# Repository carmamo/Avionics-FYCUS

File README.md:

<!-- Improved compatibility of back to top link: See: https://github.com/othneildrew/Best-README-Template/pull/73 -->

<!--
*** Thanks for checking out the Best-README-Template. If you have a suggestion
*** that would make this better, please fork the repo and create a pull request
*** or simply open an issue with the tag "enhancement".
*** Don't forget to give the project a star!
*** Thanks again! Now go create something AMAZING! :D
-->

<!-- PROJECT SHIELDS -->
<!--
*** I'm using markdown "reference style" links for readability.
*** Reference links are enclosed in brackets [ ] instead of parentheses ( ).
*** See the bottom of this document for the declaration of the reference variables
*** for contributors-url, forks-url, etc. This is an optional, concise syntax you may use.
*** https://www.markdownguide.org/basic-syntax/#reference-style-links
-->
[![Contributors][contributors-shield]][contributors-url]
[![Forks][forks-shield]][forks-url]
[![Stargazers][stars-shield]][stars-url]
[![Issues][issues-shield]][issues-url]
[![MIT License][license-shield]][license-url]
[![LinkedIn][linkedin-shield]][linkedin-url]

<!-- PROJECT LOGO -->
<br />
<div align="center">

<h3 align="center">Avionics FYCUS</h3>

  <p align="center">
    Hardware and Firmware for a 3U Cubesat
    <br />
    <a href="https://github.com/carmamo/Avionics-FYCUS"><strong>Explore the docs »</strong></a>
    <br />
    <br />
    <a href="https://github.com/carmamo/Avionics-FYCUS">View Demo</a>
    ·
    <a href="https://github.com/carmamo/Avionics-FYCUS/issues">Report Bug</a>
    ·
    <a href="https://github.com/carmamo/Avionics-FYCUS/issues">Request Feature</a>
  </p>
</div>

<!-- TABLE OF CONTENTS -->
<details>
  <summary>Table of Contents</summary>
  <ol>
    <li>
      <a href="#about-the-project">About The Project</a>
      <ul>
        <li><a href="#built-with">Built With</a></li>
      </ul>
    </li>
    <li>
      <a href="#getting-started">Getting Started</a>
      <ul>
        <li><a href="#prerequisites">Prerequisites</a></li>
        <li><a href="#installation">Installation</a></li>
      </ul>
    </li>
    <li><a href="#usage">Usage</a></li>
    <li><a href="#roadmap">Roadmap</a></li>
    <li><a href="#contributing">Contributing</a></li>
    <li><a href="#license">License</a></li>
    <li><a href="#contact">Contact</a></li>
    <li><a href="#acknowledgments">Acknowledgments</a></li>
  </ol>
</details>

<!-- ABOUT THE PROJECT -->
## About The Project
![Product front Screen Shot][product-screenshot-front]
![Product back Screen Shot][product-screenshot-back]
[![Product gui Screen Shot][gui-screenshot]][gui-screenshot]

This project involves the creation of the PCB and firmware for a 3U CubeSat, in collaboration with FYCUS, a team of passionate students at the University of Seville. Our mission is to design, manufacture and operate small satellites, and this project is a critical step in achieving that goal.

Our team will be responsible for the design and implementation of the PCB and firmware, which are essential components of the CubeSat's operation.

<p align="right">(<a href="#readme-top">back to top</a>)</p>

### Built With

<p align="right">(<a href="#readme-top">back to top</a>)</p>

<!-- GETTING STARTED -->
## Getting Started

This is an example of how you may give instructions on setting up your project locally.
To get a local copy up and running follow these simple example steps.

### Prerequisites

This is an example of how to list things you need to use the software and how to install them.
* npm
  ```sh
  npm install npm@latest -g
  ```

### Installation

1. Get a free API Key at [https://example.com](https://example.com)
2. Clone the repo
   ```sh
   git clone https://github.com/carmamo/Avionics-FYCUS.git
   ```
3. Install NPM packages
   ```sh
   npm install
   ```
4. Enter your API in `config.js`
   ```js
   const API_KEY = 'ENER YOUR API';
   ```

<p align="right">(<a href="#readme-top">back to top</a>)</p>

<!-- USAGE EXAMPLES -->
## Usage

Use this space to show useful examples of how a project can be used. Additional screenshots, code examples and demos work well in this space. You may also link to more resources.

_For more examples, please refer to the [Documentation](https://example.com)_

<p align="right">(<a href="#readme-top">back to top</a>)</p>

<!-- ROADMAP -->
## Roadmap

- [ ] Feature 1
- [ ] Feature 2
- [ ] Feature 3
    - [ ] Nested Feature

See the [open issues](https://github.com/carmamo/Avionics-FYCUS/issues) for a full list of proposed features (and known issues).

<p align="right">(<a href="#readme-top">back to top</a>)</p>

<!-- CONTRIBUTING -->
## Contributing

Contributions are what make the open source community such an amazing place to learn, inspire, and create. Any contributions you make are **greatly appreciated**.

If you have a suggestion that would make this better, please fork the repo and create a pull request. You can also simply open an issue with the tag "enhancement".
Don't forget to give the project a star! Thanks again!

1. Fork the Project
2. Create your Feature Branch (`git checkout -b feature/AmazingFeature`)
3. Commit your Changes (`git commit -m 'Add some AmazingFeature'`)
4. Push to the Branch (`git push origin feature/AmazingFeature`)
5. Open a Pull Request

<p align="right">(<a href="#readme-top">back to top</a>)</p>

<!-- LICENSE -->
## License

Distributed under the MIT License. See `LICENSE.txt` for more information.

<p align="right">(<a href="#readme-top">back to top</a>)</p>

<!-- CONTACT -->
## Contact

Your Name - [@twitter_handle](https://twitter.com/twitter_handle) - email@email_client.com

Project Link: [https://github.com/carmamo/Avionics-FYCUS](https://github.com/carmamo/Avionics-FYCUS)

<p align="right">(<a href="#readme-top">back to top</a>)</p>

<!-- ACKNOWLEDGMENTS -->
## Acknowledgments

* 
* 
* 

<p align="right">(<a href="#readme-top">back to top</a>)</p>

<!-- MARKDOWN LINKS & IMAGES -->
<!-- https://www.markdownguide.org/basic-syntax/#reference-style-links -->
[contributors-shield]: https://img.shields.io/github/contributors/carmamo/Avionics-FYCUS.svg?style=for-the-badge
[contributors-url]: https://github.com/carmamo/Avionics-FYCUS/graphs/contributors
[forks-shield]: https://img.shields.io/github/forks/carmamo/Avionics-FYCUS.svg?style=for-the-badge
[forks-url]: https://github.com/carmamo/Avionics-FYCUS/network/members
[stars-shield]: https://img.shields.io/github/stars/carmamo/Avionics-FYCUS.svg?style=for-the-badge
[stars-url]: https://github.com/carmamo/Avionics-FYCUS/stargazers
[issues-shield]: https://img.shields.io/github/issues/carmamo/Avionics-FYCUS.svg?style=for-the-badge
[issues-url]: https://github.com/carmamo/Avionics-FYCUS/issues
[license-shield]: https://img.shields.io/github/license/carmamo/Avionics-FYCUS.svg?style=for-the-badge
[license-url]: https://github.com/carmamo/Avionics-FYCUS/blob/master/LICENSE.txt
[linkedin-shield]: https://img.shields.io/badge/-LinkedIn-black.svg?style=for-the-badge&logo=linkedin&colorB=555
[linkedin-url]: https://www.linkedin.com/company/fycus/?originalSubdomain=es
[gui-screenshot]: images/screenshot2.png
[product-screenshot-front]: images/EPS_front.png
[product-screenshot-back]: images/EPS_back.png

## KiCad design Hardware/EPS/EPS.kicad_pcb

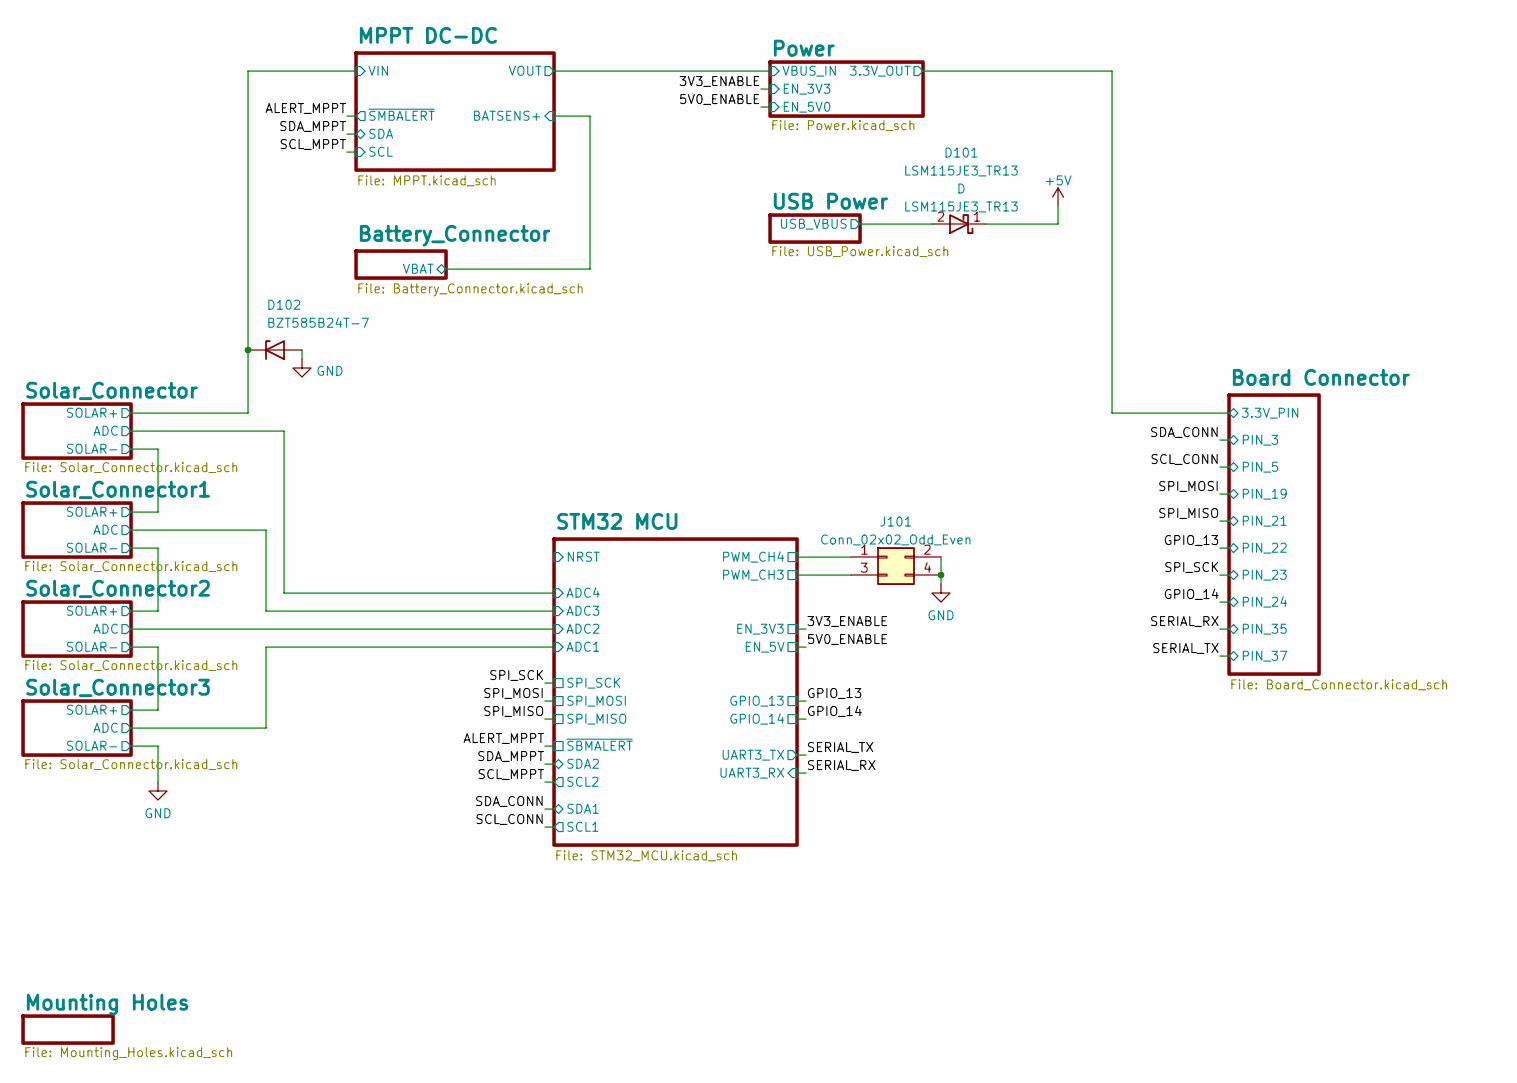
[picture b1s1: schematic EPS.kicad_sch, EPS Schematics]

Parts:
D101: LSM115JE3_TR13; DIOM5436X330N; Manufacturer_Part_Number LSM115JE3/TR13; Mouser Part Number 494-LSM115JE3/TR13
D102: BZT585B24T-7; D_SOD-523
J101: Conn_02x02_Odd_Even; PinHeader_2x02_P2.54mm_Vertical

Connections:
+5V: D101.1 (K); also elsewhere on the board
/MPPT DC-DC/VIN: D102.1 (K); also elsewhere on the board
/STM32 MCU/PWM_CH3: J101.3; also elsewhere on the board
/STM32 MCU/PWM_CH4: J101.1; also elsewhere on the board
/USB Power/USB_VBUS: D101.2 (A); also elsewhere on the board
GND: D102.2 (A), J101.2, J101.4; also elsewhere on the board

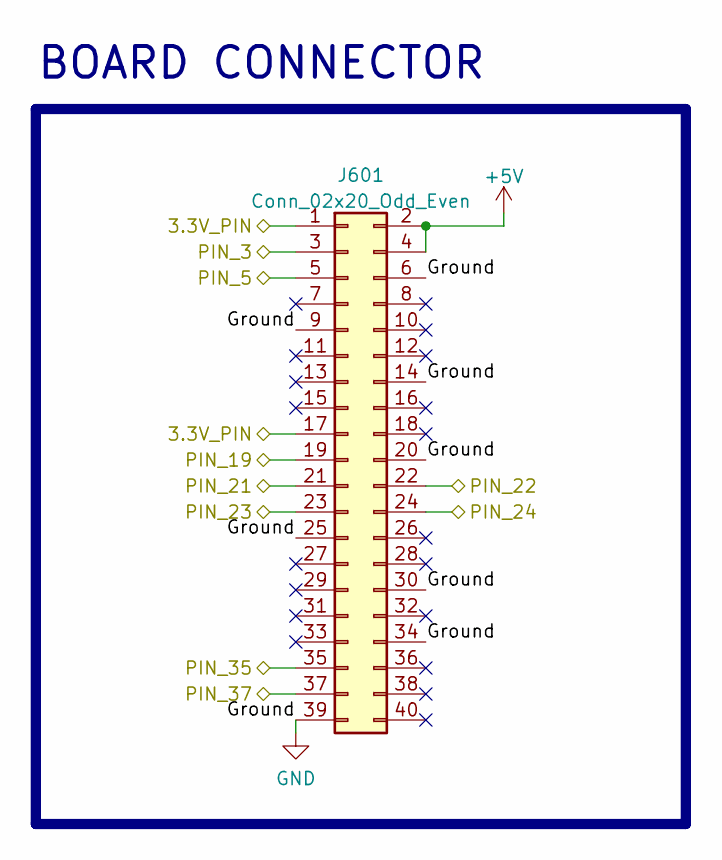
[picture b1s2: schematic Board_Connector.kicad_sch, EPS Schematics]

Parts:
J601: Conn_02x20_Odd_Even; PinHeader_2x20_P2.54mm_Vertical

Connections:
+5V: J601.2, J601.4; also elsewhere on the board
/Board Connector/3.3V_PIN: J601.1, J601.17; also elsewhere on the board
/GPIO_13: J601.22; also elsewhere on the board
/GPIO_14: J601.24; also elsewhere on the board
/SCL_CONN: J601.5; also elsewhere on the board
/SDA_CONN: J601.3; also elsewhere on the board
/SERIAL_RX: J601.35; also elsewhere on the board
/SERIAL_TX: J601.37; also elsewhere on the board
/SPI_MISO: J601.21; also elsewhere on the board
/SPI_MOSI: J601.19; also elsewhere on the board
/SPI_SCK: J601.23; also elsewhere on the board
GND: J601.6, J601.9, J601.14, J601.20, J601.25, J601.30, J601.34, J601.39; also elsewhere on the board

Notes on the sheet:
BOARD CONNECTOR

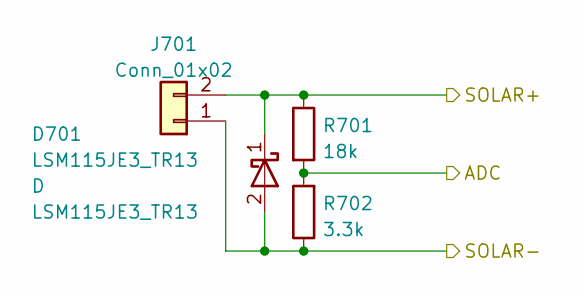
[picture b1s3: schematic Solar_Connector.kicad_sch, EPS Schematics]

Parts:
D701: LSM115JE3_TR13; DIOM5436X330N; Manufacturer_Part_Number LSM115JE3/TR13; Mouser Part Number 494-LSM115JE3/TR13
J701: Conn_01x02; JST_PH_S2B-PH-K_1x02_P2.00mm_Horizontal
R701: 18k; R_0603_1608Metric_Pad0.98x0.95mm_HandSolder
R702: 3.3k; R_0603_1608Metric_Pad0.98x0.95mm_HandSolder

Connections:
/MPPT DC-DC/VIN: D701.1 (K), J701.2, R701.1; also elsewhere on the board
/STM32 MCU/ADC4: R701.2, R702.2; also elsewhere on the board
/Solar_Connector/SOLAR-: D701.2 (A), J701.1, R702.1; also elsewhere on the board

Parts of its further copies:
D801, D901, D1001: LSM115JE3_TR13; DIOM5436X330N; Manufacturer_Part_Number LSM115JE3/TR13; Mouser Part Number 494-LSM115JE3/TR13
J801, J901, J1001: Conn_01x02; JST_PH_S2B-PH-K_1x02_P2.00mm_Horizontal
R801, R901, R1001: 18k; R_0603_1608Metric_Pad0.98x0.95mm_HandSolder
R802, R902, R1002: 3.3k; R_0603_1608Metric_Pad0.98x0.95mm_HandSolder

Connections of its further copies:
/STM32 MCU/ADC1: R1001.2, R1002.2; also elsewhere on the board
/STM32 MCU/ADC2: R901.2, R902.2; also elsewhere on the board
/STM32 MCU/ADC3: R801.2, R802.2; also elsewhere on the board
/Solar_Connector1/SOLAR-: D801.2 (A), D901.1 (K), J801.1, J901.2, R802.1, R901.1
/Solar_Connector2/SOLAR-: D901.2 (A), D1001.1 (K), J901.1, J1001.2, R902.1, R1001.1
/Solar_Connector/SOLAR-: D801.1 (K), J801.2, R801.1; also elsewhere on the board
GND: D1001.2 (A), J1001.1, R1002.1; also elsewhere on the board

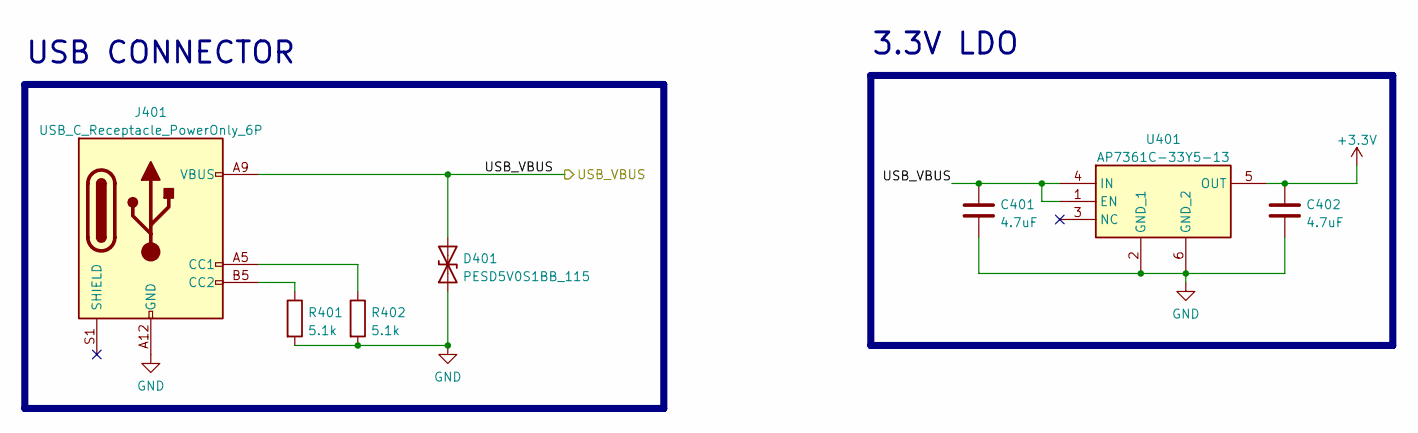
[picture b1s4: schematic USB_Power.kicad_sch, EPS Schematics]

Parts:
C401, C402: 4.7uF; C_0603_1608Metric_Pad1.08x0.95mm_HandSolder
D401: PESD5V0S1BB_115; D_SOD-523
J401: USB_C_Receptacle_PowerOnly_6P; USB_C_Receptacle_GCT_USB4135-GF-A_6P_TopMnt_Horizontal
R401, R402: 5.1k; R_0603_1608Metric_Pad0.98x0.95mm_HandSolder
U401: AP7361C-33Y5-13; AP7361C25Y513; Manufacturer_Part_Number AP7361C-25Y5-13; Mouser Part Number 621-AP7361C-25Y5-13

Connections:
+3.3V: C402.1, U401.5 (OUT); also elsewhere on the board
/USB Power/USB_VBUS: C401.1, D401.2 (A2), J401.A9 (VBUS), J401.B9 (VBUS), U401.1 (EN), U401.4 (IN); also elsewhere on the board
GND: C401.2, C402.2, D401.1 (A1), J401.A12 (GND), J401.B12 (GND), R401.2, R402.2, U401.2 (GND_1), U401.6 (GND_2); also elsewhere on the board
unnamed: J401.A5 (CC1), R402.1
unnamed: J401.B5 (CC2), R401.1

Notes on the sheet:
USB CONNECTOR
3.3V LDO

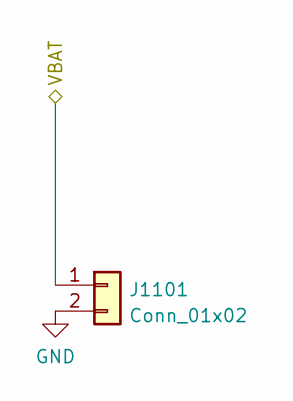
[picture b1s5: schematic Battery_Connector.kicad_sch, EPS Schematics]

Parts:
J1101: Conn_01x02; JST_PH_S2B-PH-K_1x02_P2.00mm_Horizontal

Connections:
/Battery_Connector/VBAT: J1101.1; also elsewhere on the board
GND: J1101.2; also elsewhere on the board

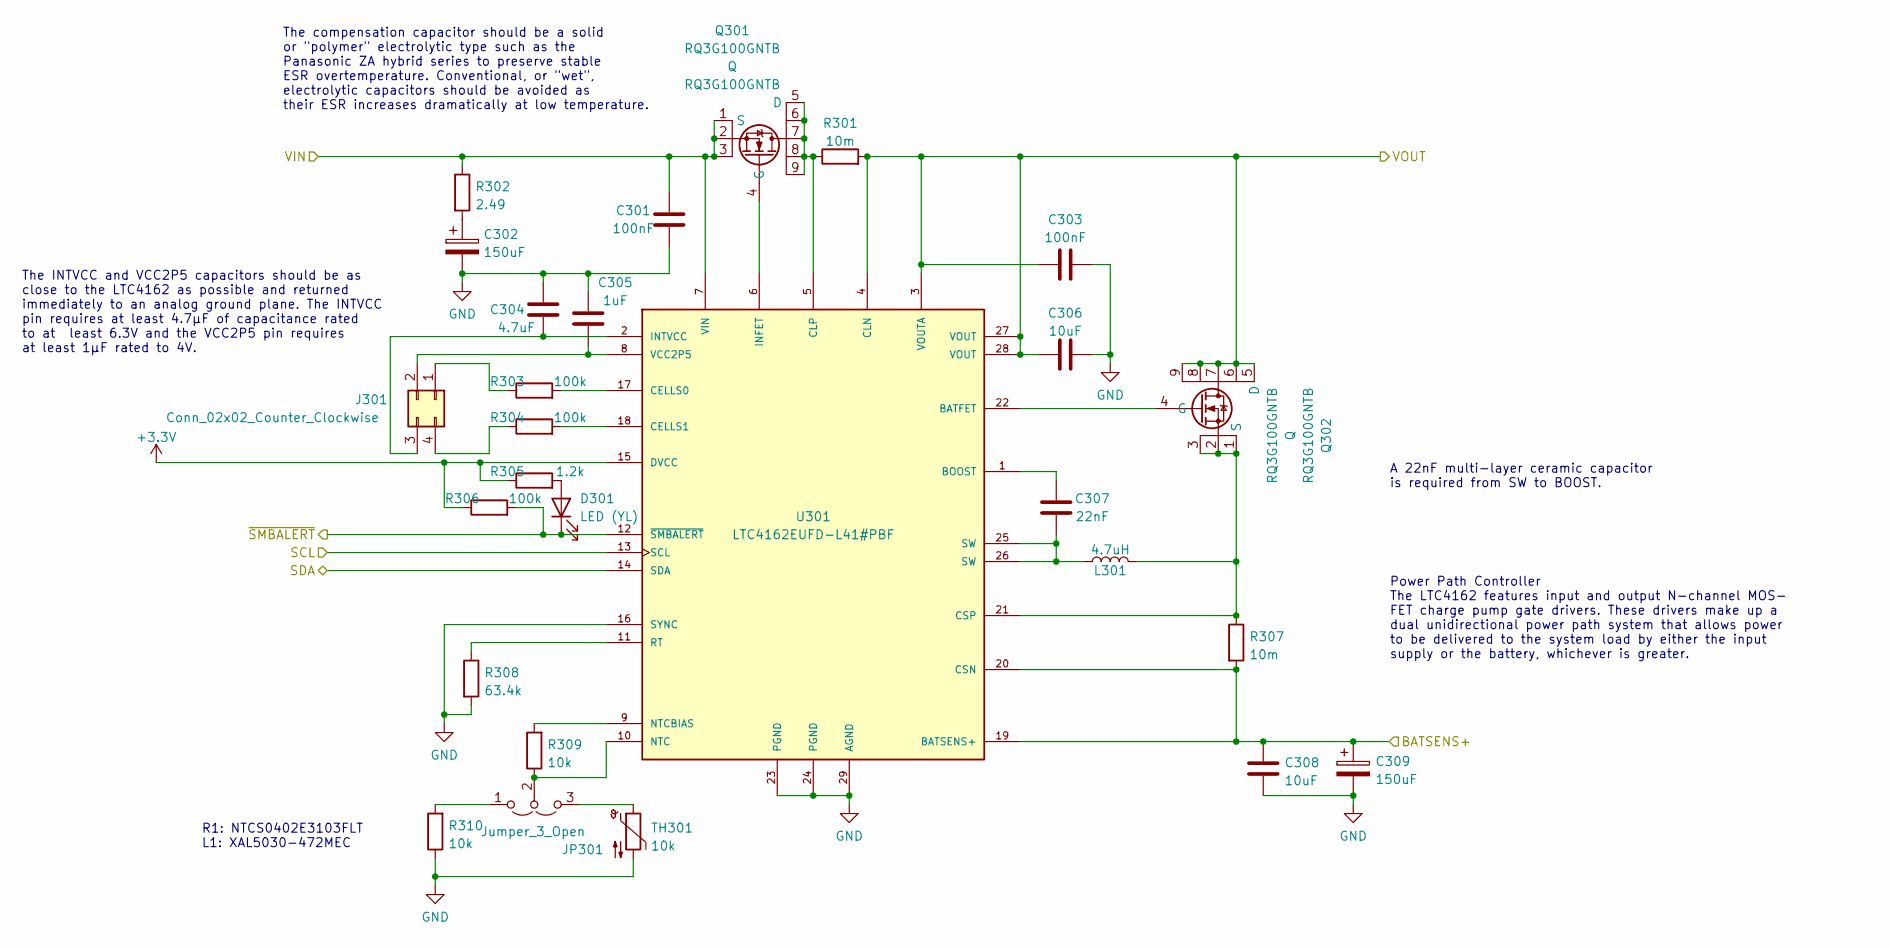
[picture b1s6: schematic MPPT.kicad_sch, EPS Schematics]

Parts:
C301, C303: 100nF; C_0603_1608Metric_Pad1.08x0.95mm_HandSolder
C302, C309: 150uF; CAP_EEHZS1H151V
C304: 4.7uF; C_0603_1608Metric_Pad1.08x0.95mm_HandSolder
C305: 1uF; C_0603_1608Metric_Pad1.08x0.95mm_HandSolder
C306, C308: 10uF; C_1206_3216Metric_Pad1.33x1.80mm_HandSolder
C307: 22nF; C_0603_1608Metric_Pad1.08x0.95mm_HandSolder
D301: LED (YL); LED_0603_1608Metric
J301: Conn_02x02_Counter_Clockwise; PinHeader_2x02_P2.54mm_Vertical
JP301: Jumper_3_Open; PinHeader_1x03_P2.54mm_Vertical
L301: 4.7uH; XAL1060222MEB
Q301, Q302: RQ3G100GNTB; Mouser Part Number 755-RQ3G100GNTB
R301, R307: 10m; R_0805_2012Metric_Pad1.20x1.40mm_HandSolder
R302: 2.49; R_1206_3216Metric_Pad1.30x1.75mm_HandSolder
R303, R304, R306: 100k; R_0603_1608Metric_Pad0.98x0.95mm_HandSolder
R305: 1.2k; R_0603_1608Metric_Pad0.98x0.95mm_HandSolder
R308: 63.4k; R_0603_1608Metric_Pad0.98x0.95mm_HandSolder
R309, R310: 10k; R_0603_1608Metric_Pad0.98x0.95mm_HandSolder
TH301: 10k; PinHeader_1x02_P1.00mm_Vertical
U301: LTC4162EUFD-L41#PBF; QFN50P500X400X80-29N; PARTREV A

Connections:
+3.3V: R305.1, R306.1, U301.15 (DVCC); also elsewhere on the board
/ALERT_MPPT: D301.1 (K), R306.2, U301.12 (~SMBALERT); also elsewhere on the board
/Battery_Connector/VBAT: C308.1, C309.1, R307.2, U301.19 (BATSENS+), U301.20 (CSN); also elsewhere on the board
/MPPT DC-DC/VIN: C301.1, Q301.1 (S), Q301.2, Q301.3, R302.1, U301.7 (VIN); also elsewhere on the board
/MPPT DC-DC/VOUT: C303.1, C306.1, Q302.5 (D), Q302.6, Q302.7, Q302.8, Q302.9, R301.2, U301.3 (VOUTA), U301.4 (CLN), U301.27 (VOUT), U301.28 (VOUT); also elsewhere on the board
/SCL_MPPT: U301.13 (SCL); also elsewhere on the board
/SDA_MPPT: U301.14 (SDA); also elsewhere on the board
GND: C301.2, C302.2, C303.2, C304.2, C305.2, C306.2, C308.2, C309.2, R308.2, R310.1, TH301.2, U301.16 (SYNC), U301.23 (PGND), U301.24 (PGND), U301.29 (AGND); also elsewhere on the board
unnamed: C302.1, R302.2
unnamed: C304.1, J301.3, U301.2 (INTVCC)
unnamed: C305.1, J301.2, U301.8 (VCC2P5)
unnamed: C307.1, U301.1 (BOOST)
unnamed: C307.2, L301.1, U301.25 (SW), U301.26 (SW)
unnamed: D301.2 (A), R305.2
unnamed: J301.1, R303.1
unnamed: J301.4, R304.1
unnamed: JP301.1 (A), R310.2
unnamed: JP301.2 (C), R309.1, U301.10 (NTC)
unnamed: JP301.3 (B), TH301.1
unnamed: L301.2, Q302.1 (S), Q302.2, Q302.3, R307.1, U301.21 (CSP)
unnamed: Q301.4 (G), U301.6 (INFET)
unnamed: Q301.5 (D), Q301.6, Q301.7, Q301.8, Q301.9, R301.1, U301.5 (CLP)
unnamed: Q302.4 (G), U301.22 (BATFET)
unnamed: R303.2, U301.17 (CELLS0)
unnamed: R304.2, U301.18 (CELLS1)
unnamed: R308.1, U301.11 (RT)
unnamed: R309.2, U301.9 (NTCBIAS)

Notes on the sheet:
The INTVCC and VCC2P5 capacitors should be as close to the LTC4162 as possible and returned immediately to an analog ground plane. The INTVCC pin requires at least 4.7μF of capacitance rated to at least 6.3V and the VCC2P5 pin requires at least 1μF rated to 4V.
A 22nF multi-layer ceramic capacitor is required from SW to BOOST.
Power Path Controller The LTC4162 features input and output N-channel MOS- FET charge pump gate drivers. These drivers make up a dual unidirectional power path system that allows power to be delivered to the system load by either the input supply or the battery, whichever is greater.
R1: NTCS0402E3103FLT L1: XAL5030-472MEC
The compensation capacitor should be a solid or "polymer" electrolytic type such as the Panasonic ZA hybrid series to preserve stable ESR overtemperature. Conventional, or "wet", electrolytic capacitors should be avoided as their ESR increases dramatically at low temperature.

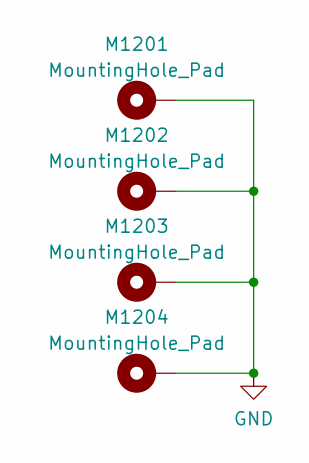
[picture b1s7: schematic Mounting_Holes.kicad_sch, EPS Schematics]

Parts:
M1201, M1202, M1203, M1204: MountingHole_Pad; MountingHole_3.2mm_M3_Pad_Via

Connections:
GND: M1201.1, M1202.1, M1203.1, M1204.1; also elsewhere on the board

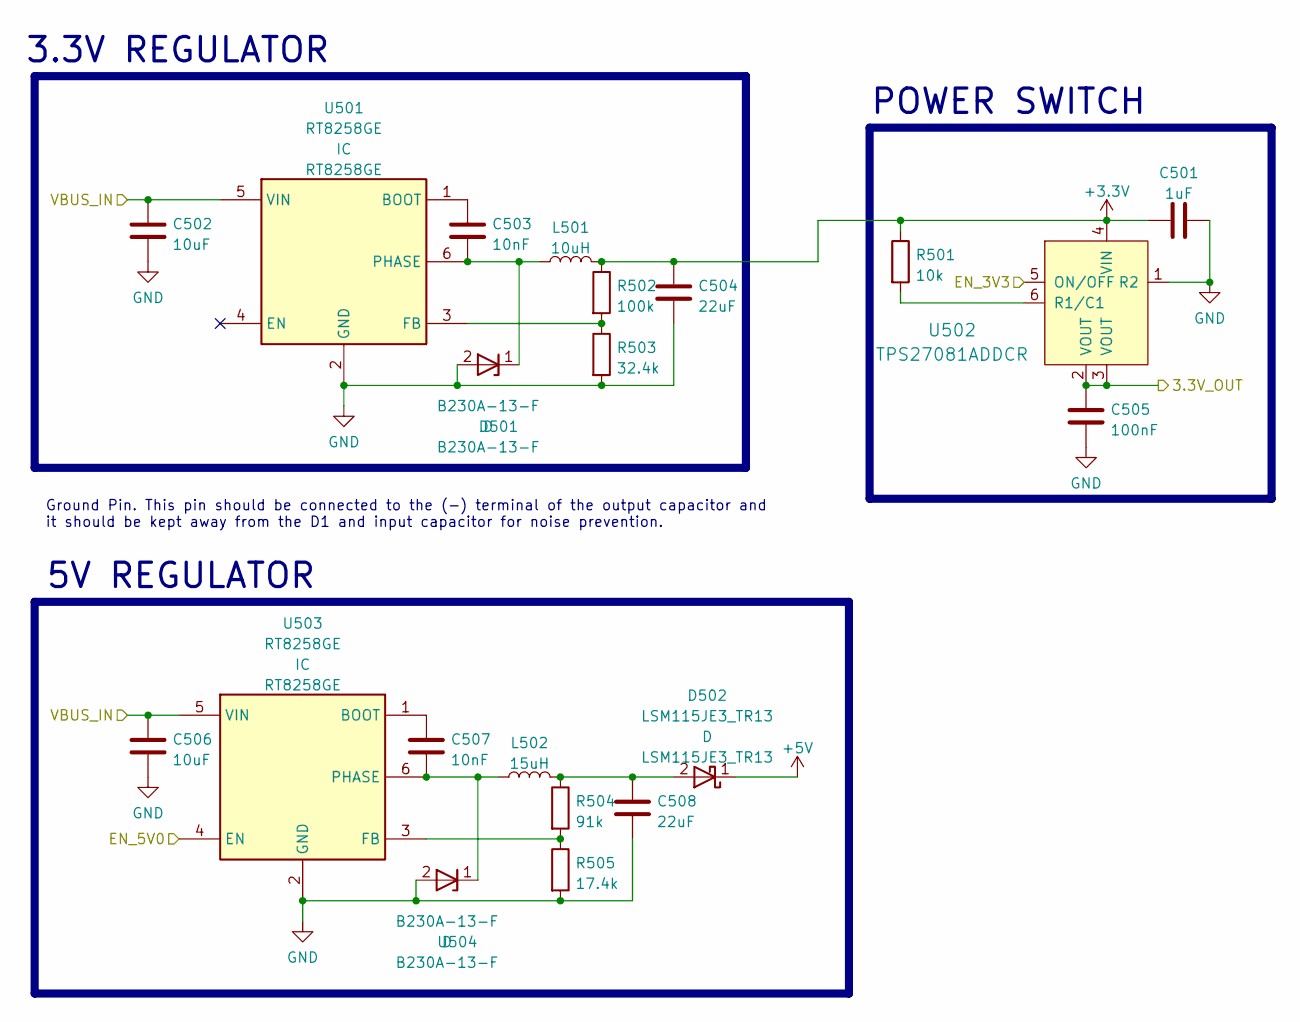
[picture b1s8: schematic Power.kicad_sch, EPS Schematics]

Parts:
C501: 1uF; C_0603_1608Metric_Pad1.08x0.95mm_HandSolder
C502, C506: 10uF; C_0603_1608Metric_Pad1.08x0.95mm_HandSolder
C503, C507: 10nF; C_0603_1608Metric_Pad1.08x0.95mm_HandSolder
C504, C508: 22uF; C_0603_1608Metric_Pad1.08x0.95mm_HandSolder
C505: 100nF; C_0603_1608Metric_Pad1.08x0.95mm_HandSolder
D501: B230A-13-F; DIOM5226X230N; Manufacturer_Part_Number B230A-13-F; Mouser Part Number 621-B230A-F
D502: LSM115JE3_TR13; DIOM5436X330N; Manufacturer_Part_Number LSM115JE3/TR13; Mouser Part Number 494-LSM115JE3/TR13
L501: 10uH; SLF12555T
L502: 15uH; SLF12565
R501: 10k; R_0603_1608Metric_Pad0.98x0.95mm_HandSolder
R502: 100k; R_0603_1608Metric_Pad0.98x0.95mm_HandSolder
R503: 32.4k; R_0603_1608Metric_Pad0.98x0.95mm_HandSolder
R504: 91k; R_0603_1608Metric_Pad0.98x0.95mm_HandSolder
R505: 17.4k; R_0603_1608Metric_Pad0.98x0.95mm_HandSolder
U501, U503: RT8258GE; SOT94P279X130-6N; Manufacturer_Part_Number RT8258GE
U502: TPS27081ADDCR; SOT-23-6; MPN TPS27081ADDCR; Digi-Key_PN 296-34970-1-ND
U504: B230A-13-F; DIOM5226X230N; Manufacturer_Part_Number B230A-13-F; Mouser Part Number 621-B230A-F

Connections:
+3.3V: C501.2, C504.1, L501.2, R501.1, R502.1, U502.4 (VIN); also elsewhere on the board
+5V: D502.1 (K); also elsewhere on the board
/3V3_ENABLE: U502.5 (ON/OFF); also elsewhere on the board
/5V0_ENABLE: U503.4 (EN); also elsewhere on the board
/Board Connector/3.3V_PIN: C505.1, U502.2 (VOUT), U502.3 (VOUT); also elsewhere on the board
/MPPT DC-DC/VOUT: C502.1, C506.1, U501.5 (VIN), U503.5 (VIN); also elsewhere on the board
GND: C501.1, C502.2, C504.2, C505.2, C506.2, C508.2, D501.2 (A), R503.2, R505.2, U501.2 (GND), U502.1 (R2), U503.2 (GND), U504.2 (A); also elsewhere on the board
unnamed: C503.1, U501.1 (BOOT)
unnamed: C503.2, D501.1 (K), L501.1, U501.6 (PHASE)
unnamed: C507.1, U503.1 (BOOT)
unnamed: C507.2, L502.1, U503.6 (PHASE), U504.1 (K)
unnamed: C508.1, D502.2 (A), L502.2, R504.1
unnamed: R501.2, U502.6 (R1/C1)
unnamed: R502.2, R503.1, U501.3 (FB)
unnamed: R504.2, R505.1, U503.3 (FB)

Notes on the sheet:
3.3V REGULATOR
POWER SWITCH
Ground Pin. This pin should be connected to the (-) terminal of the output capacitor and it should be kept away from the D1 and input capacitor for noise prevention.
5V REGULATOR

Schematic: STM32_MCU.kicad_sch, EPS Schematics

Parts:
C201: 4.7uF; C_0603_1608Metric_Pad1.08x0.95mm_HandSolder
C202, C203, C204, C205, C208: 100nF; C_0603_1608Metric_Pad1.08x0.95mm_HandSolder
C206: 1uF; C_0603_1608Metric_Pad1.08x0.95mm_HandSolder
C207: 10nF; C_0603_1608Metric_Pad1.08x0.95mm_HandSolder
C210, C211: 6pF; C_0603_1608Metric_Pad1.08x0.95mm_HandSolder
D201: LED_R; LED_0603_1608Metric
D202: LED_G; LED_0603_1608Metric
D203: LED_YL; LED_0603_1608Metric
J201: Conn_ARM_JTAG_SWD_10; PinHeader_2x05_P2.00mm_Vertical
R201, R202, R203, R204: 4.7k; R_0603_1608Metric_Pad0.98x0.95mm_HandSolder
R205, R206: 130; R_0603_1608Metric_Pad0.98x0.95mm_HandSolder
R207: 120; R_0603_1608Metric_Pad0.98x0.95mm_HandSolder
R208: 10k; R_0603_1608Metric_Pad0.98x0.95mm_HandSolder
R209: 3.3k; R_0603_1608Metric_Pad0.98x0.95mm_HandSolder
U201: STM32L431RCT; LQFP-64
U202: HZ0805E601R-10; BEADC2012X90N; Manufacturer_Part_Number HZ0805E601R-10
Y201: NX5032GA-8.000M-STD-CSU-1; XTAL_NX5032_NDK

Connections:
+3.3V: C201.1, C202.1, C203.1, C204.1, C205.1, J201.1 (VTref), R201.1, R202.2, R203.1, R204.2, R205.1, R206.1, R207.1, U201.1 (VBAT), U201.19 (VDD), U201.32 (VDD), U201.48 (VDD), U201.64 (VDD), U202.1; also elsewhere on the board
/3V3_ENABLE: U201.41 (PA8); also elsewhere on the board
/5V0_ENABLE: U201.40 (PC9); also elsewhere on the board
/ALERT_MPPT: U201.36 (PB15); also elsewhere on the board
/GPIO_13: U201.2 (PC13); also elsewhere on the board
/GPIO_14: U201.3 (PC14-OSC32_IN); also elsewhere on the board
/SCL_CONN: R201.2, U201.61 (PB8); also elsewhere on the board
/SCL_MPPT: R203.2, U201.34 (I2C2_SCL); also elsewhere on the board
/SDA_CONN: R202.1, U201.62 (PB9); also elsewhere on the board
/SDA_MPPT: R204.1, U201.35 (I2C2_SDA); also elsewhere on the board
/SERIAL_RX: U201.52 (PC11); also elsewhere on the board
/SERIAL_TX: U201.51 (PC10); also elsewhere on the board
/SPI_MISO: U201.44 (PA11); also elsewhere on the board
/SPI_MOSI: U201.45 (PA12); also elsewhere on the board
/SPI_SCK: U201.15 (PA1); also elsewhere on the board
/STM32 MCU/ADC1: U201.22 (PA6); also elsewhere on the board
/STM32 MCU/ADC2: U201.23 (PA7); also elsewhere on the board
/STM32 MCU/ADC3: U201.24 (PC4); also elsewhere on the board
/STM32 MCU/ADC4: U201.25 (PC5); also elsewhere on the board
/STM32 MCU/BOOT0: R208.1, U201.60 (PH3/BOOT0)
/STM32 MCU/HSE_IN: C210.1, U201.5 (RCC_OSC_IN), Y201.2
/STM32 MCU/HSE_OUT: R209.1, U201.6 (RCC_OSC_OUT)
/STM32 MCU/JTCK: J201.4 (SWDCLK/TCK), U201.49 (SYS_JTCK-SWCLK)
/STM32 MCU/JTDI: J201.8 (NC/TDI), U201.50 (SYS_JTDI)
/STM32 MCU/JTDO: J201.6 (SWO/TDO), U201.55 (SYS_JTDO-SWO)
/STM32 MCU/JTMS: J201.2 (SWDIO/TMS), U201.46 (SYS_JTMS-SWDIO)
/STM32 MCU/LED_G: D202.1 (K), U201.10 (ADC1_IN3)
/STM32 MCU/LED_R: D201.1 (K), U201.9 (ADC1_IN2)
/STM32 MCU/LED_YL: D203.1 (K), U201.11 (ADC1_IN4)
/STM32 MCU/PWM_CH3: U201.29 (PB10); also elsewhere on the board
/STM32 MCU/PWM_CH4: U201.30 (PB11); also elsewhere on the board
GND: C201.2, C202.2, C203.2, C204.2, C205.2, C206.2, C207.2, C208.2, C210.2, C211.2, J201.3 (GND), J201.5 (GND), J201.9 (GNDDetect), R208.2, U201.12 (VSSA/VREF-), U201.18 (VSS), U201.31 (VSS), U201.47 (VSS), U201.63 (VSS); also elsewhere on the board
unnamed: C211.1, R209.2, Y201.1
unnamed: D201.2 (A), R205.2
unnamed: D202.2 (A), R206.2
unnamed: D203.2 (A), R207.2

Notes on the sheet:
Rext must be 3316 Ohms aprox. so resistor measurement is advised to get as close as possible.
HSE CRYSTAL RESONATOR
BOOT PULL-DOWN
LEDS
I2C PULL-UPS
STM32 MCU
DECOUPLING
JTAG

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
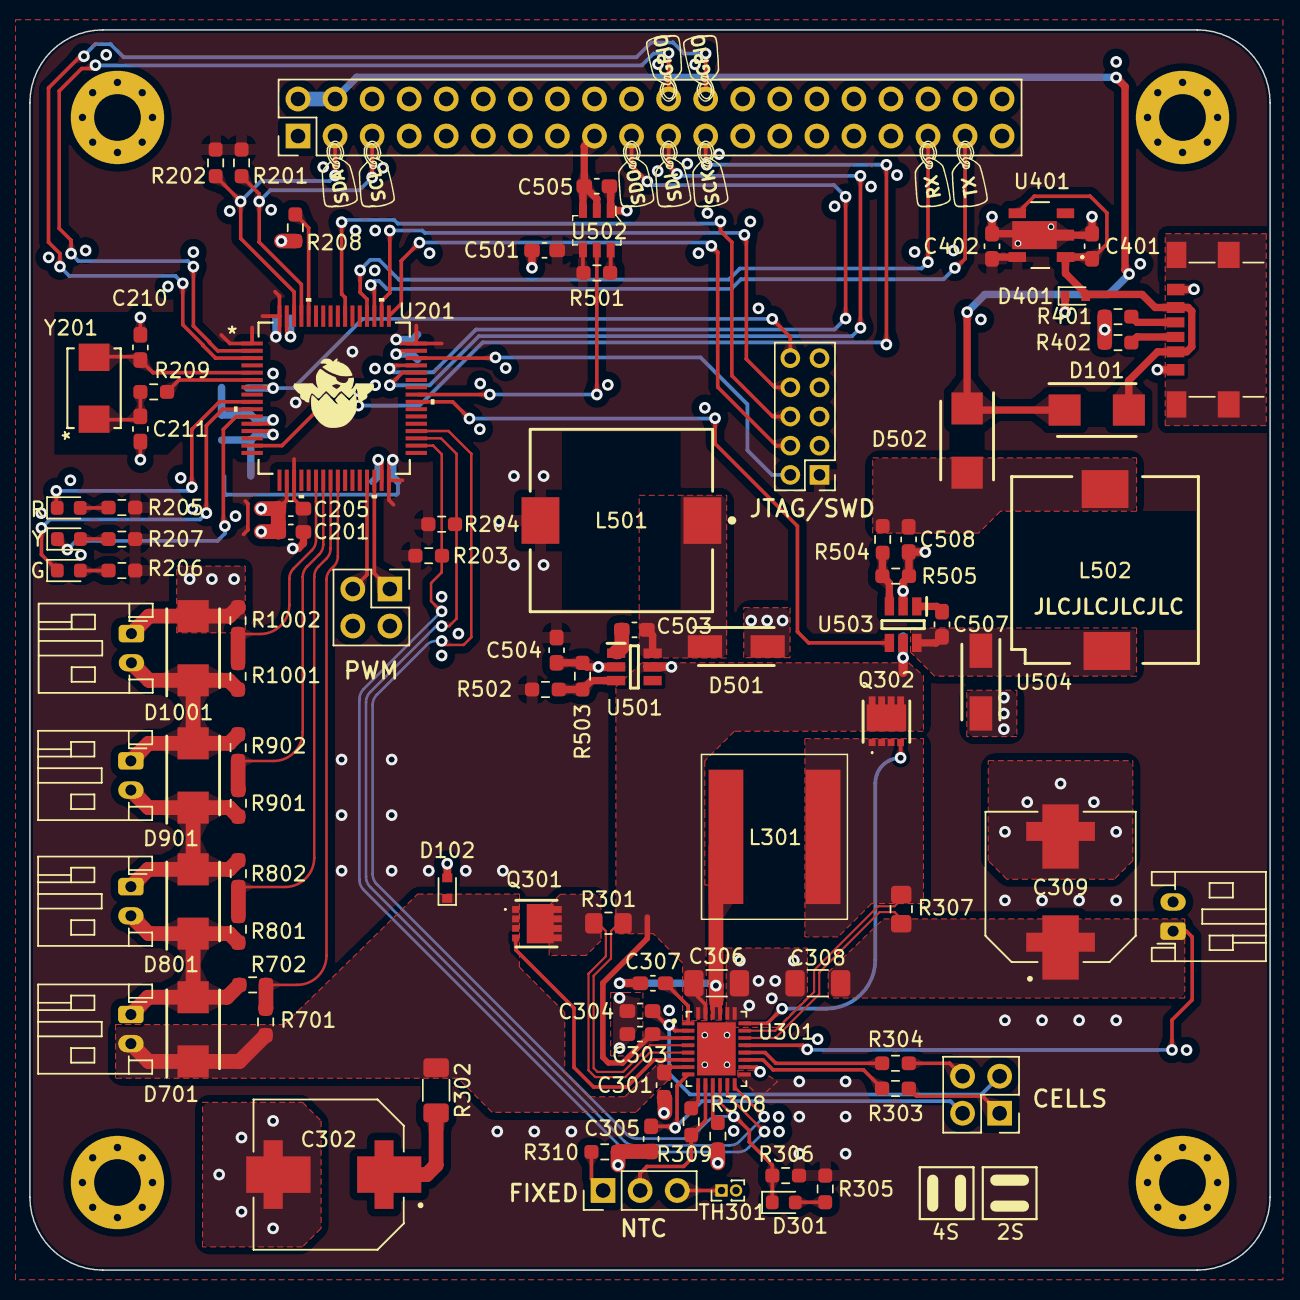
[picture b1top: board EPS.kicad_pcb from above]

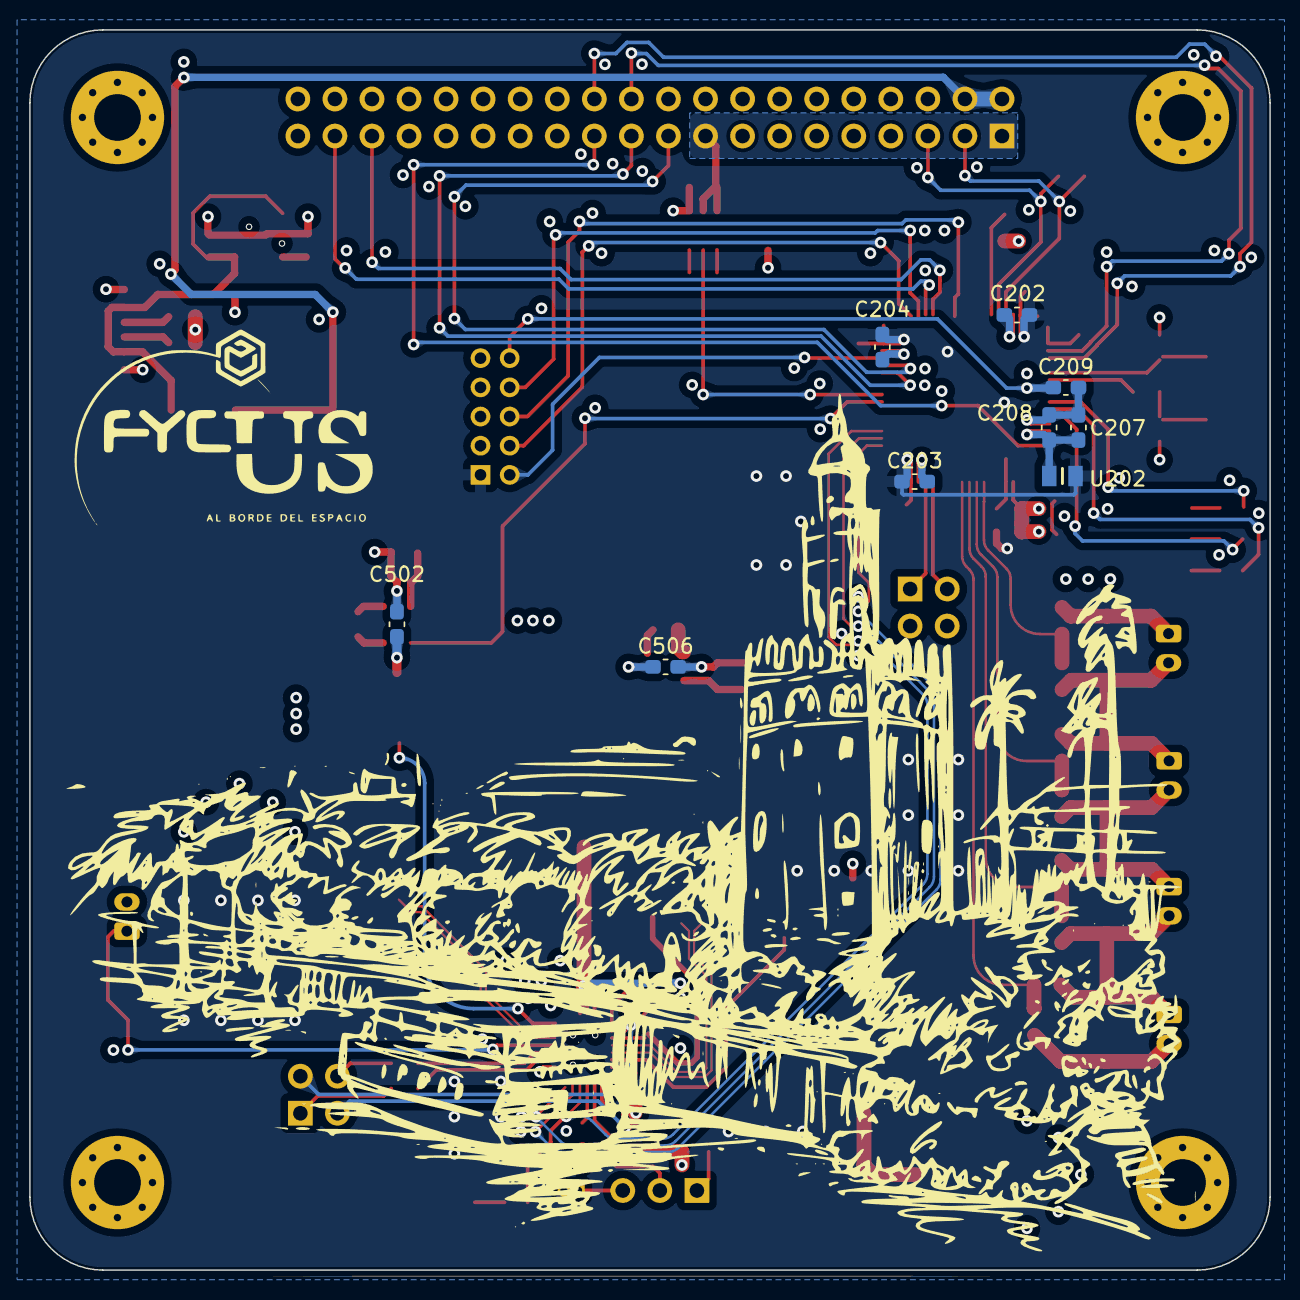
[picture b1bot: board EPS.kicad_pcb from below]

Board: 4 copper layers, 85.0 x 85.0 mm, 108 parts (10 on the bottom side), 76 nets.

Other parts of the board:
C209: 100nF; C_0603_1608Metric_Pad1.08x0.95mm_HandSolder
G001, G002: LOGO

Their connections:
GND: C209.2; also elsewhere on the board

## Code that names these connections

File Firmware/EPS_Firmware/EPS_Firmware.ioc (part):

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Mcu.Name=STM32L431R(B-C)Tx
Mcu.Package=LQFP64
Mcu.UserName=STM32L431RCTx
PA1.Mode=Full_Duplex_Master
PA1.Signal=SPI1_SCK
PA11.Mode=Full_Duplex_Master
PA11.Signal=SPI1_MISO
PA12.Mode=Full_Duplex_Master
PA12.Signal=SPI1_MOSI
PA13\ (JTMS-SWDIO).Mode=JTAG_5_pins
PA13\ (JTMS-SWDIO).Signal=SYS_JTMS-SWDIO
PA14\ (JTCK-SWCLK).Mode=JTAG_5_pins
PA14\ (JTCK-SWCLK).Signal=SYS_JTCK-SWCLK
PA15\ (JTDI).Mode=JTAG_5_pins
PA15\ (JTDI).Signal=SYS_JTDI
PA8.GPIOParameters=GPIO_Label
PA8.GPIO_Label=EN_3V3
PA8.Signal=GPIO_Output
PB10.Signal=S_TIM2_CH3
PB11.Signal=S_TIM2_CH4
PB13.Mode=I2C
PB13.Signal=I2C2_SCL
PB14.Mode=I2C
PB14.Signal=I2C2_SDA
PB15.GPIOParameters=GPIO_Label
PB15.GPIO_Label=SBMALERT
PB15.Signal=GPXTI15
PB3\ (JTDO-TRACESWO).Mode=JTAG_5_pins
PB3\ (JTDO-TRACESWO).Signal=SYS_JTDO-SWO
PB4\ (NJTRST).Mode=JTAG_5_pins
PB4\ (NJTRST).Signal=SYS_JTRST
PB8.Mode=I2C
PB8.Signal=I2C1_SCL
PB9.Mode=I2C
PB9.Signal=I2C1_SDA
PC1.GPIOParameters=PinState,GPIO_Label
PC1.GPIO_Label=LED_R
PC1.PinState=GPIO_PIN_SET
PC1.Signal=GPIO_Output
PC10.Mode=Asynchronous
PC10.Signal=USART3_TX
PC11.Mode=Asynchronous
PC11.Signal=USART3_RX
PC13.Signal=GPXTI13
PC14-OSC32_IN\ (PC14).Signal=GPXTI14
PC2.GPIOParameters=PinState,GPIO_PuPd,GPIO_Label
PC2.GPIO_Label=LED_G
PC2.GPIO_PuPd=GPIO_NOPULL
PC2.PinState=GPIO_PIN_SET
PC2.Signal=GPIO_Output
PC3.GPIOParameters=PinState,GPIO_Label
PC3.GPIO_Label=LED_YL
PC3.PinState=GPIO_PIN_RESET
PC3.Signal=GPIO_Output
PC9.GPIOParameters=GPIO_Label
PC9.GPIO_Label=EN_5V
PC9.Signal=GPIO_Output
PH0-OSC_IN\ (PH0).Mode=HSE-External-Oscillator
PH0-OSC_IN\ (PH0).Signal=RCC_OSC_IN
PH1-OSC_OUT\ (PH1).Mode=HSE-External-Oscillator
PH1-OSC_OUT\ (PH1).Signal=RCC_OSC_OUT
RCC.HSE_VALUE=20000000
RCC.SYSCLKFreq_VALUE=80000000
RCC.SYSCLKSource=RCC_SYSCLKSOURCE_PLLCLK
board=custom

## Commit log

2023-03-24 Added Project Files
2023-03-24 Added Readme Template
2023-03-25 Edit README
    Fixing README
    Added LTC4162 footprint and symbol
    README Edit
    More README
2023-03-26 Created Schematic for LTC4162
    Added Comments
2023-03-26 Added USB, Solar Connector and MATLAB Folder
2023-03-27 Added interboard connector and MCU
2023-03-28 Added board connector layout
2023-03-28 updating some comments
2023-04-02 IMU, GPS and Magnetometer blocks (Altium)
2023-04-02 Added Power sheet and ESD Protection
2023-04-06 EPS v0.0.1
2023-04-08 Fuse, Power Switch to 3.3V, connector ESD Prot.
    v0.0.2
2023-04-09 Reworked LTC4162 Symbol
2023-04-09 Defined pinout for board connector, major revision
    v0.0.3 - Fixed erratas and cleaned the schematic
2023-04-11 Added Live Script for Prediction
2023-04-13 Added geo2chart
2023-04-13 MPPT IC Routing & layout
2023-04-13 First submission to repository :D
2023-04-13 Gs-Sat vector calculation
2023-04-16 new updated code with normal editor
2023-04-16 windrose pic for code
2023-04-16 MPPT & Power layout finished
2023-04-17 Changed uC pinout and finished uC routing
2023-04-18 Finished XTAL layout
2023-04-19 Finished EPS - v0.1.0
2023-04-20 Created Payload Board
2023-05-05 Updated to KiCAD 7.0
2023-08-04 Update, no changes. Blinky test on EPS HW
2023-08-17 Blinky Test on FC
2023-10-08 Prelaunch tweaks
2023-10-15 Add files via upload
    Programa para hacer las fotos y vídeos con la raspberry
2023-10-16 Debugging Memory Leaks
